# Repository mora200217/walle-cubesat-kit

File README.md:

# 🌱 walle-cubesat-kit
 - [Diseño PCB](#pcb-design).
 - [Diseño Estructura](#estructura).
 - [Codigo](#codigo).

## PCB Design
El diseño de la PCB se realizó en Kicad 8.0.8.  
Esquematico: [TPI_v1.kicad_sch](PCB/TPI_v1.kicad_sch)  
Archivo PCB: [TPI_v1.kicad_pcb](PCB/TPI_v1.kicad_pcb)  
Archivos Gerber: [Fabric.rar](PCB/Fabric/Fabric.rar)

### Esquematico

## Codigo

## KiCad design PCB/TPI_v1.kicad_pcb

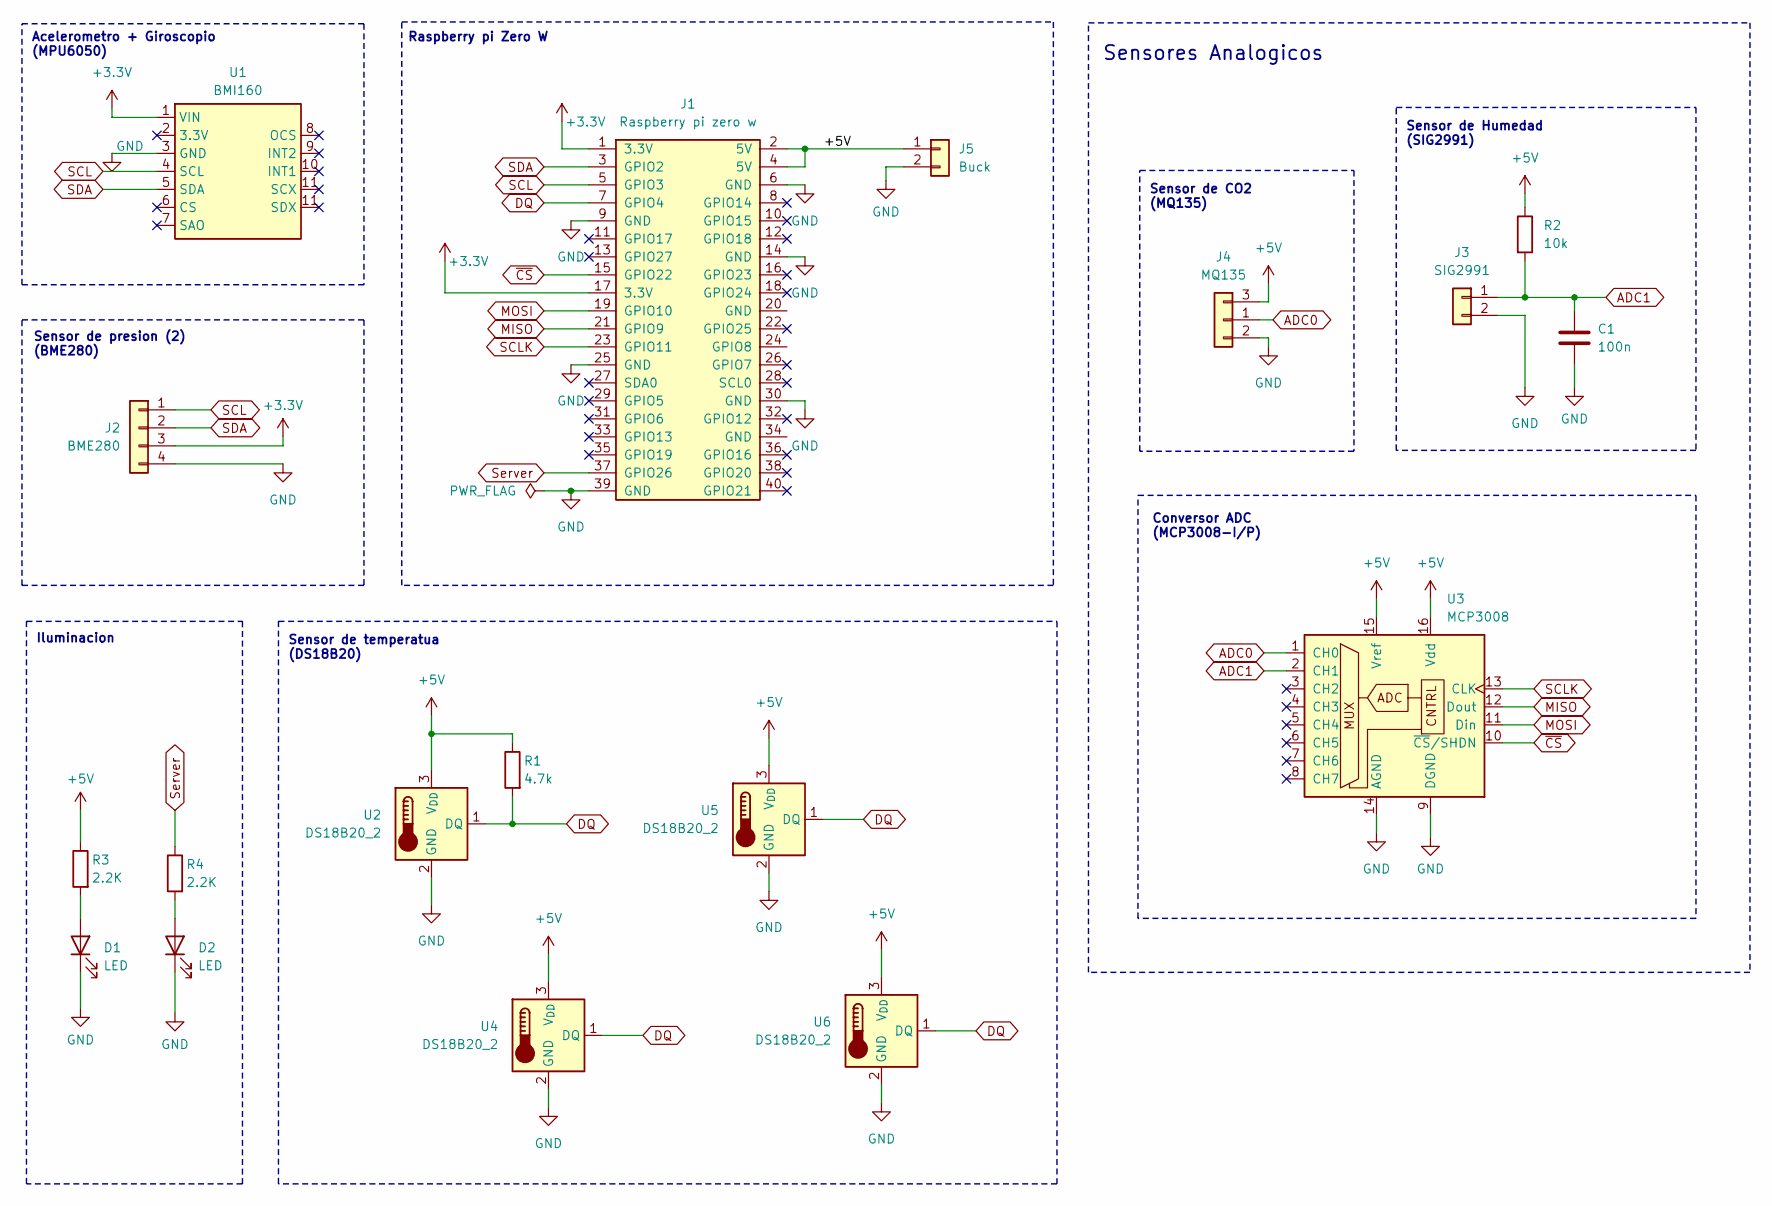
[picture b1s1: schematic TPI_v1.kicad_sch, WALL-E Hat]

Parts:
C1: 100n; C_Disc_D3.0mm_W1.6mm_P2.50mm
D1, D2: LED; LED_D3.0mm
J1: Raspberry pi zero w; PinHeader_2x20_P2.54mm_Vertical
J2: BME280; JST_XH_B4B-XH-A_1x04_P2.50mm_Vertical
J3: SIG2991; JST_XH_S2B-XH-A-1_1x02_P2.50mm_Horizontal
J4: MQ135; JST_XH_S3B-XH-A-1_1x03_P2.50mm_Horizontal
J5: Buck; PinSocket_2x01_P2.54mm_Vertical
R1: 4.7k; R_Axial_DIN0207_L6.3mm_D2.5mm_P7.62mm_Horizontal
R2: 10k; R_Axial_DIN0207_L6.3mm_D2.5mm_P7.62mm_Horizontal
R3, R4: 2.2K; R_Axial_DIN0207_L6.3mm_D2.5mm_P7.62mm_Horizontal
U1: BMI160
U2, U4: DS18B20_2; JST_XH_S3B-XH-A-1_1x03_P2.50mm_Horizontal
U3: MCP3008; DIP-16_W7.62mm
U5, U6: DS18B20_2; JST_XH_B3B-XH-A_1x03_P2.50mm_Vertical

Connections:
+3.3V: J1.1 (3.3V), J1.17 (3.3V), J2.3, U1.1 (VIN)
+5V: J1.2 (5V), J1.4 (5V), J4.3 (Pin_1), J5.1, R1.1, R2.1, R3.1, U2.3 (V_{DD}), U3.15 (Vref), U3.16 (Vdd), U4.3 (V_{DD}), U5.3 (V_{DD}), U6.3 (V_{DD})
ADC0: J4.1 (Pin_2), U3.1 (CH0)
ADC1: C1.1, J3.1, R2.2, U3.2 (CH1)
DQ: J1.7 (GPIO4), R1.2, U2.1 (DQ), U4.1 (DQ), U5.1 (DQ), U6.1 (DQ)
GND: C1.2, D1.1 (K), D2.1 (K), J1.6 (GND), J1.9 (GND), J1.14 (GND), J1.25 (GND), J1.30 (GND), J1.39 (GND), J2.4, J3.2, J4.2 (Pin_3), J5.2, U1.3 (GND), U2.2 (GND), U3.9 (DGND), U3.14 (AGND), U4.2 (GND), U5.2 (GND), U6.2 (GND)
MISO: J1.21 (GPIO9), U3.12 (Dout)
MOSI: J1.19 (GPIO10), U3.11 (Din)
unnamed: D1.2 (A), R3.2
unnamed: D2.2 (A), R4.2
SCL: J1.5 (GPIO3), J2.1, U1.4 (SCL)
SCLK: J1.23 (GPIO11), U3.13 (CLK)
SDA: J1.3 (GPIO2), J2.2, U1.5 (SDA)
Server: J1.37 (GPIO26), R4.1
~CS: J1.15 (GPIO22), U3.10 (~CS/SHDN)

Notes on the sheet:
Sensor de presion (2) (BME280)
Raspberry pi Zero W
Sensor de Humedad (SIG2991)
Conversor ADC (MCP3008-I/P)
Iluminacion
Sensor de temperatua (DS18B20)
Sensores Analogicos
Sensor de CO2 (MQ135)
Acelerometro + Giroscopio (MPU6050)

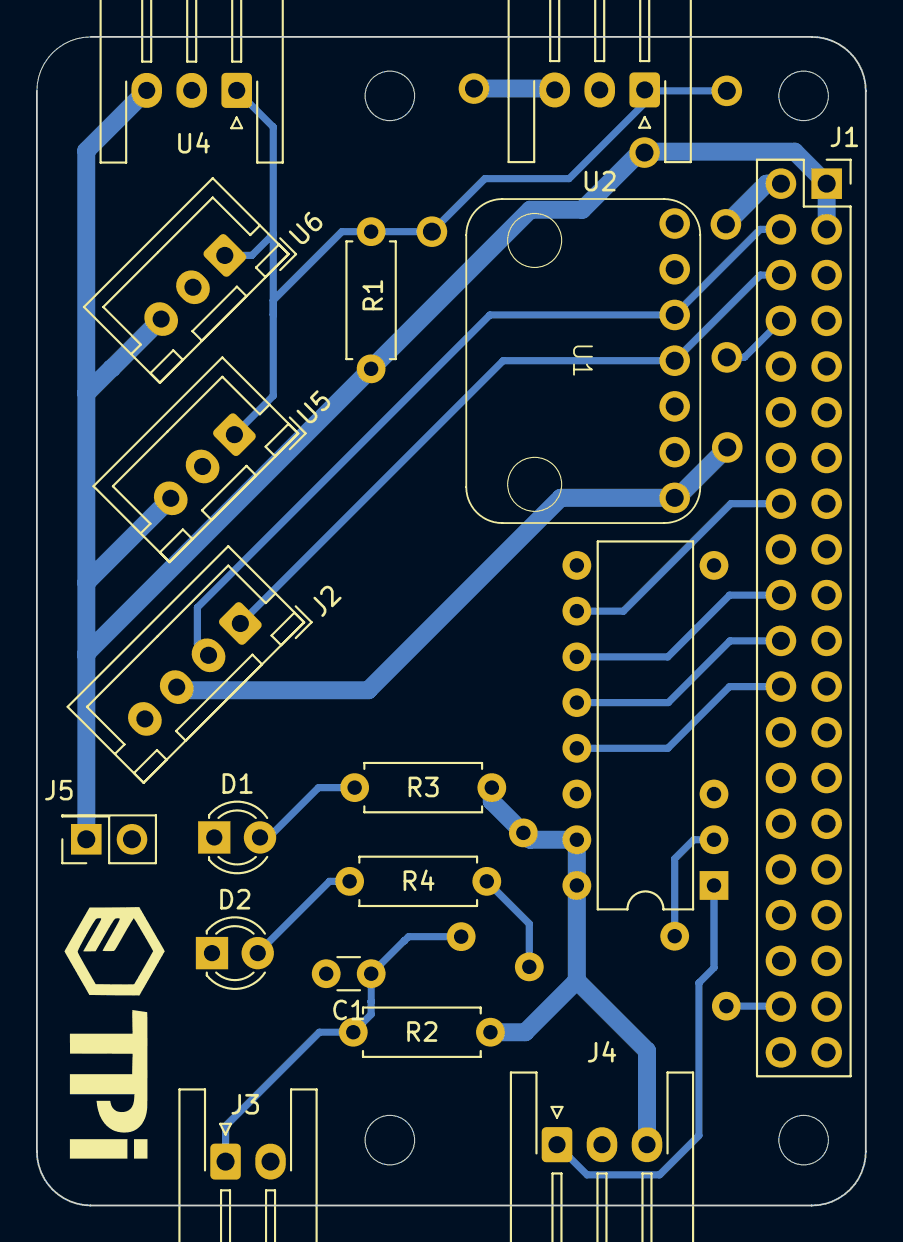
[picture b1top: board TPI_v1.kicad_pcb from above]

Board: 2 copper layers, 46.1 x 64.9 mm, 18 parts (0 on the bottom side), 15 nets.

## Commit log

2025-02-13 [New] Base in nextjs
2025-02-17 Create a
2025-02-19 PCB update
2025-02-19 [Update] sensor
2025-02-19 [Update] sensor bMI
2025-02-19 [Update] Correction with I2C communication"
2025-02-20 [Update ]Autocalibrate
2025-02-20 [Update]
2025-02-20 [Update] offset
2025-02-20 PCB
    Se cambio el voltaje del sensor BME280
2025-02-20 PDFs
2025-02-21 BME
    Se mejoro el codigo del bme280
2025-02-21 Submit gerbers
2025-02-23 [Update] camera functional
2025-02-23 Update Sensors
2025-02-23 Sensors
2025-02-23 MQ135
2025-02-24 [New] Chart base. Better oganization folder in project root
2025-02-24 Update sensors
    Cambio del available como atributo en vez de funcion
2025-02-24 [Prueba]
2025-02-25 New DS18B20
2025-02-26 PCB update
    V2 PCB
2025-02-26 General update
